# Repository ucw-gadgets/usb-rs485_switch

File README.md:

# usb-rs485_switch
8x RS-485 switch and USB convertor

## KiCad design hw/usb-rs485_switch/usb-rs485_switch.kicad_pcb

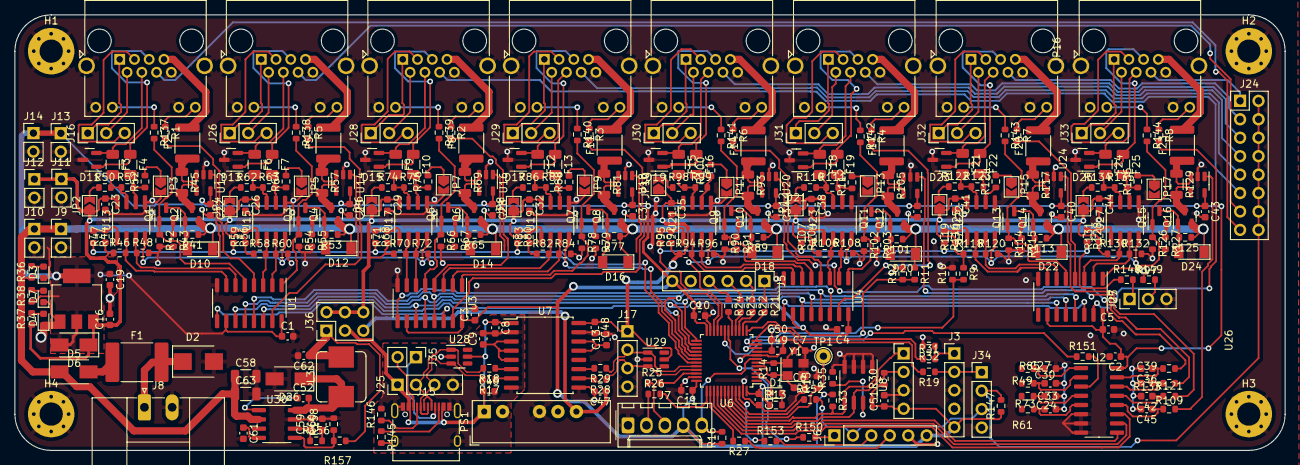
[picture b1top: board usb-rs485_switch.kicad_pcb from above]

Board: 2 copper layers, 175.0 x 60.0 mm, 357 parts (0 on the bottom side), 279 nets.

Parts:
C1, C2, C3, C4, C5, C8, C9, C10, C11, C12, C13, C22, C23, C24, C25, C26, C27, C28, C29, C30, C31, C32, C33, C34, C35, C36, C37, C38, C39, C40, C41, C42, C43, C44, C45, C48, C49, C51, C52: 100n; C_0603_1608Metric
C6, C7: C; C_0603_1608Metric
C16, C47: 10u; C_0603_1608Metric
C19: 22u; C_0603_1608Metric
C46: 4u7; C_0603_1608Metric
C50: 1u; C_0603_1608Metric
C58, C63: 4u7/50V; C_1206_3216Metric
C59, C61: 8.2n; C_0603_1608Metric
C60: 22n; C_0603_1608Metric
C62: 22u/6.3V X5R; C_0603_1608Metric
D1: USR_LED; LED_0603_1608Metric
D2: SM6T27A; D_SMB
D3: VCC_LED; LED_0603_1608Metric
D4: 5V_LED; LED_0603_1608Metric
D5, D6: SS54; D_SMA
D7: 3V3_LED; LED_0603_1608Metric
D10, D12, D14, D16, D18, D20, D22, D24: ZMM5V6; D_MiniMELF
D11, D13, D15, D17, D19, D21, D23, D25: PSM712-LF-T7; SOT-23
D26: SS14; D_SMA
F1: Polyfuse; Fuse_2920_7451Metric
F2, F5, F8, F11, F14, F17, F20, F23: BSMD1812-110-33V; Fuse_1812_4532Metric
F3, F4, F6, F7, F9, F10, F12, F13, F15, F16, F18, F19, F21, F22, F24, F25: BSMD1206-010-60V; Fuse_1206_3216Metric
H1, H2, H3, H4: MountingHole_Pad; MountingHole_3.2mm_M3_Pad_Via
J1, J2, J18, J19, J20, J21, J22, J23: RJ45_LED_Shielded; RJ45_Amphenol_RJHSE538X
J3: USART2; PinHeader_1x05_P2.54mm_Vertical
J4: I2C; PinHeader_1x04_P2.54mm_Vertical
J5: SPI; PinHeader_1x06_P2.54mm_Vertical
J6: GPIO; PinHeader_1x06_P2.54mm_Vertical
J7: PROG; Molex_KK-254_AE-6410-05A_1x05_P2.54mm_Vertical
J8: POWER; PhoenixContact_MC_1,5_2-GF-3.81_1x02_P3.81mm_Horizontal_Thr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
J9: VCC_OUT1; PinHeader_1x02_P2.54mm_Vertical
J10: VCC_OUT2; PinHeader_1x02_P2.54mm_Vertical
J11: 5V_OUT1; PinHeader_1x02_P2.54mm_Vertical
J12: 5V_OUT2; PinHeader_1x02_P2.54mm_Vertical
J13: 3V_OUT1; PinHeader_1x02_P2.54mm_Vertical
J14: 3V3_OUT2; PinHeader_1x02_P2.54mm_Vertical
J15: MC-107DM; USB_C_Receptacle_XKB_U262-16XN-4BVC11
J16: RES1; PinHeader_1x03_P2.54mm_Vertical
J17: USB_NONISO; PinHeader_1x04_P2.54mm_Vertical
J24: 1WIRE_CHANNELS; PinHeader_2x08_P2.54mm_Vertical
J25: USB_ISO; PinHeader_1x04_P2.54mm_Vertical
J26: RES2; PinHeader_1x03_P2.54mm_Vertical
J27: USART3; PinHeader_1x03_P2.54mm_Vertical
J28: RES3; PinHeader_1x03_P2.54mm_Vertical
J29: RES4; PinHeader_1x03_P2.54mm_Vertical
J30: RES5; PinHeader_1x03_P2.54mm_Vertical
J31: RES6; PinHeader_1x03_P2.54mm_Vertical
J32: RES7; PinHeader_1x03_P2.54mm_Vertical
J33: RES8; PinHeader_1x03_P2.54mm_Vertical
J34: 1WIRE_SELECT; PinHeader_1x04_P2.54mm_Vertical
J35: USB-C_SBU; PinHeader_1x02_P2.54mm_Vertical
J36: PWR_SELECT; PinHeader_2x03_P2.54mm_Vertical
JP2, JP3, JP4, JP5, JP6, JP7, JP8, JP9, JP10, JP11, JP12, JP13, JP14, JP15, JP16, JP17: SolderJumper_2_Open; SolderJumper-2_P1.3mm_Open_TrianglePad1.0x1.5mm
L3: 47u; L_Bourns_SRP7028A_7.3x6.6mm
PS1: IA0505S; Converter_DCDC_XP_POWER-IAxxxxS_THT
Q1, Q3, Q5, Q7, Q9, Q11, Q13, Q15: MMBT5551; SOT-23
Q2, Q4, Q6, Q8, Q10, Q12, Q14, Q16: Si2301CDS; SOT-23
R1, R2, R3, R4, R5, R6, R7, R8, R41, R53, R65, R77, R89, R101, R113, R125: 1k; R_0603_1608Metric
R9, R10, R11, R12, R13, R14, R15, R16, R31, R32, R35, R36, R37, R38, R148, R149, R156, R157, R158: R; R_0603_1608Metric
R17, R18, R28, R29: 24R; R_0603_1608Metric
R19, R21, R22, R23, R24, R25, R26, R27, R44, R56, R68, R80, R92, R104, R116, R128, R150, R151, R152, R153: 330R; R_0603_1608Metric
R30, R33, R147: 4k7; R_0603_1608Metric
R42, R46, R47, R48, R54, R58, R59, R60, R66, R70, R71, R72, R78, R82, R83, R84, R90, R94, R95, R96, R102, R106, R107, R108, R114, R118, R119, R120, R126, R130, R131, R132: 10k; R_0603_1608Metric
R43, R55, R67, R79, R91, R103, R115, R127, R137, R138, R139, R140, R141, R142, R143, R144: 2k7; R_0603_1608Metric
R45, R57, R69, R81, R93, R105, R117, R129: 0R1; R_1206_3216Metric
R49, R61, R73, R85, R97, R109, R121, R133: 100k; R_0603_1608Metric
R50, R52, R62, R64, R74, R76, R86, R88, R98, R100, R110, R112, R122, R124, R134, R136: 720R; R_0603_1608Metric
R51, R63, R75, R87, R99, R111, R123, R135: 120R; R_0603_1608Metric
R145, R146: 5k1; R_0603_1608Metric
TP1: BOOT0; TestPoint_THTPad_D2.0mm_Drill1.0mm
U1, U3, U4, U5: 74HC595; SOIC-16_3.9x9.9mm_P1.27mm
U2: CD4051B; SOIC-16_3.9x9.9mm_P1.27mm
U6: STM32F103C8Tx; LQFP-48_7x7mm_P0.5mm
U7: ADUM4160; SOIC-16W_7.5x10.3mm_P1.27mm
U8: M24C01-WMN; SOIC-8_3.9x4.9mm_P1.27mm
U11: AMS1117-3.3; SOT-223-3_TabPin2
U12, U14, U16, U18, U20, U22, U24, U26: INA180A1; SOT-23-5
U13, U15, U17, U19, U21, U23, U25, U27: MAX485E; SOIC-8_3.9x4.9mm_P1.27mm
U28, U29: SRV05-4; SOT-23-6
U30: TPS54331; SOIC-8_3.9x4.9mm_P1.27mm
Y1: Crystal_GND23; Crystal_SMD_3225-4Pin_3.2x2.5mm

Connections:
+3V3: C1.1, C2.1, C3.1, C4.1, C5.1, C10.1, C11.1, C12.1, C19.1, C22.1, C25.1, C28.1, C31.1, C34.1, C37.1, C40.1, C43.1, C49.1, C50.1, C51.1, D6.2 (A), J3.5, J4.4, J5.6, J6.6, J7.4, J13.1, J14.1, R13.1, R16.1, R30.1, R33.1, R38.1, R147.1, U1.10 (~SRCLR), U1.16 (VCC), U2.16 (VDD), U3.10 (~SRCLR), U3.16 (VCC), U4.10 (~SRCLR), U4.16 (VCC), U5.10 (~SRCLR), U5.16 (VCC), U6.9 (VDDA), U6.24 (VDD), U6.36 (VDD), U6.48 (VDD), U8.8 (VCC), U11.2 (VO), U12.5 (VS), U14.5 (VS), U16.5 (VS), U18.5 (VS), U20.5 (VS), U22.5 (VS), U24.5 (VS), U26.5 (VS)
+5V: C16.1, C23.1, C26.1, C29.1, C32.1, C35.1, C38.1, C41.1, C44.1, C48.1, D6.1 (K), J11.1, J12.1, J17.1, J36.2, J36.4, J36.6, JP2.1 (A), JP4.1 (A), JP6.1 (A), JP8.1 (A), JP10.1 (A), JP12.1 (A), JP14.1 (A), JP16.1 (A), R9.1, R37.1, R46.1, R47.1, R58.1, R59.1, R70.1, R71.1, R82.1, R83.1, R94.1, R95.1, R106.1, R107.1, R118.1, R119.1, R130.1, R131.1, U7.16 (VBUS2), U11.3 (VI), U13.8 (VCC), U15.8 (VCC), U17.8 (VCC), U19.8 (VCC), U21.8 (VCC), U23.8 (VCC), U25.8 (VCC), U27.8 (VCC), U29.5 (VP)
/1WIRE: J24.2, J24.4, J24.6, J24.8, J24.10, J24.12, J24.14, J24.16, J34.2, R147.2
/1WIRE1: J1.6, J24.15
/1WIRE2: J2.6, J24.13
/1WIRE3: J18.6, J24.11
/1WIRE4: J19.6, J24.9
/1WIRE5: J20.6, J24.7
/1WIRE6: J21.6, J24.5
/1WIRE7: J22.6, J24.3
/1WIRE8: J23.6, J24.1
/5V_DCDC: C62.1, J36.1, L3.2, R157.1
/5V_SENSE: R9.2, R10.1, U6.11 (PA1)
/5V_USB_ISO: C47.1, J36.5, PS1.6 (+Vout)
/GPIO0: J6.1, R150.2
/GPIO1: J6.2, J34.3, R152.2
/GPIO2: J6.3, R153.2
/GPIO3: J6.4, R27.1
/I2C1_SCL: J4.2, R30.2, U6.42 (PB6), U8.6 (SCL)
/I2C1_SDA: J4.1, R33.2, U6.43 (PB7), U8.5 (SDA)
/I_SENSE: R151.2, U2.3 (X)
/I_SENSE1: C24.1, R49.1, U2.1 (X4)
/I_SENSE2: C27.1, R61.1, U2.5 (X5)
/I_SENSE3: C30.1, R73.1, U2.2 (X6)
/I_SENSE4: C33.1, R85.1, U2.4 (X7)
/I_SENSE5: C36.1, R97.1, U2.15 (X2)
/I_SENSE6: C39.1, R109.1, U2.14 (X1)
/I_SENSE7: C42.1, R121.1, U2.13 (X0)
/I_SENSE8: C45.1, R133.1, U2.12 (X3)
/I_SEN_A: U2.11 (A), U6.39 (PB3)
/I_SEN_B: U2.10 (B), U6.40 (PB4)
/I_SEN_C: U2.9 (C), U6.41 (PB5)
/LED_G1: J1.12, R1.1
/LED_G2: J2.12, R5.1
/LED_G3: J18.12, R2.1
/LED_G4: J19.12, R3.1
/LED_G5: J20.12, R6.1
/LED_G6: J21.12, R4.1
/LED_G7: J22.12, R7.1
/LED_G8: J23.12, R8.1
/NRST: J7.5, R16.2, U6.7 (NRST)
/PWR_EN1: Q1.1 (B), R42.1, R137.2, U1.5 (QF)
/PWR_EN2: Q3.1 (B), R54.1, R138.2, U1.1 (QB)
/PWR_EN3: Q5.1 (B), R66.1, R139.2, U3.5 (QF)
/PWR_EN4: Q7.1 (B), R78.1, R140.2, U3.1 (QB)
/PWR_EN5: Q9.1 (B), R90.1, R141.2, U4.5 (QF)
/PWR_EN6: Q11.1 (B), R102.1, R142.2, U4.1 (QB)
/PWR_EN7: Q13.1 (B), R114.1, R143.2, U5.5 (QF)
/PWR_EN8: Q15.1 (B), R126.1, R144.2, U5.1 (QB)
/RS485 Line driver/A: D11.1 (A1), F4.1, J1.5
/RS485 Line driver/B: D11.2 (A2), F3.1, J1.4
/RS485 Line driver/PWR_OUT: F2.2, J1.7
/SPI1_MISO: J5.3, R23.1
/SPI1_MOSI: J5.4, R24.1
/SPI1_SCK: J5.2, R22.1
/SPI2_MOSI: U1.14 (SER), U6.28 (PB15)
/SPI2_SCK: U1.11 (SRCLK), U3.11 (SRCLK), U4.11 (SRCLK), U5.11 (SRCLK), U6.26 (PB13)
/SPI2_STROBE: U1.12 (RCLK), U3.12 (RCLK), U4.12 (RCLK), U5.12 (RCLK), U6.25 (PB12)
/SWCLK: J7.2, R26.1
/SWDIO: J7.3, R25.1
/TX_EN1: R48.1, U1.6 (QG), U13.3 (DE)
/TX_EN2: R60.1, U1.2 (QC), U15.3 (DE)
/TX_EN3: R72.1, U3.6 (QG), U17.3 (DE)
/TX_EN4: R84.1, U3.2 (QC), U19.3 (DE)
/TX_EN5: R96.1, U4.6 (QG), U21.3 (DE)
/TX_EN6: R108.1, U4.2 (QC), U23.3 (DE)
/TX_EN7: R120.1, U5.6 (QG), U25.3 (DE)
/TX_EN8: R132.1, U5.2 (QC), U27.3 (DE)
/USART1_RX: R44.2, R56.2, R68.2, R80.2, U6.31 (PA10)
/USART1_TX: U6.30 (PA9), U13.4 (DI), U15.4 (DI), U17.4 (DI), U19.4 (DI)
/USART2_RX: R31.1, U6.13 (PA3)
/USART2_TX: J3.2, J34.1, R19.1
/USART3_RX: R92.2, R104.2, R116.2, R128.2, R148.1, U6.22 (PB11)
/USART3_TX: R149.1, U6.21 (PB10), U21.4 (DI), U23.4 (DI), U25.4 (DI), U27.4 (DI)
/USB_DN: J17.2, R29.1, U6.32 (PA11), U29.1 (IO1)
/USB_DP: J17.3, R28.1, U6.33 (PA12), U29.3 (IO2)
/USB_IN_N: J15.A7 (D-), J15.B7 (D-), J25.2, R18.2, U28.1 (IO1)
/USB_IN_P: J15.A6 (D+), J15.B6 (D+), J25.3, R17.2, U28.3 (IO2)
/VCC_SENSE: R11.2, R12.1, U6.10 (PA0)
/sheet620AF7C7/A: D17.1 (A1), F13.1, J19.5
/sheet620AF7C7/B: D17.2 (A2), F12.1, J19.4
/sheet620AF7C7/PWR_OUT: F11.2, J19.7
/sheet620CBEF1/A: D19.1 (A1), F16.1, J20.5
/sheet620CBEF1/B: D19.2 (A2), F15.1, J20.4
/sheet620CBEF1/PWR_OUT: F14.2, J20.7
/sheet620CBEF2/A: D21.1 (A1), F19.1, J21.5
/sheet620CBEF2/B: D21.2 (A2), F18.1, J21.4
/sheet620CBEF2/PWR_OUT: F17.2, J21.7
/sheet620CBEF3/A: D23.1 (A1), F22.1, J22.5
/sheet620CBEF3/B: D23.2 (A2), F21.1, J22.4
/sheet620CBEF3/PWR_OUT: F20.2, J22.7
/sheet620CBEF4/A: D25.1 (A1), F25.1, J23.5
/sheet620CBEF4/B: D25.2 (A2), F24.1, J23.4
/sheet620CBEF4/PWR_OUT: F23.2, J23.7
/sheet6205AD21/A: D13.1 (A1), F7.1, J2.5
/sheet6205AD21/B: D13.2 (A2), F6.1, J2.4
/sheet6205AD21/PWR_OUT: F5.2, J2.7
/sheet62070CF7/A: D15.1 (A1), F10.1, J18.5
/sheet62070CF7/B: D15.2 (A2), F9.1, J18.4
/sheet62070CF7/PWR_OUT: F8.2, J18.7
/~RX_EN1: R46.2, U1.7 (QH), U13.2 (~RE)
/~RX_EN2: R58.2, U1.3 (QD), U15.2 (~RE)
/~RX_EN3: R70.2, U3.7 (QH), U17.2 (~RE)
/~RX_EN4: R82.2, U3.3 (QD), U19.2 (~RE)
/~RX_EN5: R94.2, U4.7 (QH), U21.2 (~RE)
/~RX_EN6: R106.2, U4.3 (QD), U23.2 (~RE)
/~RX_EN7: R118.2, U5.7 (QH), U25.2 (~RE)
/~RX_EN8: R130.2, U5.3 (QD), U27.2 (~RE)
/~SPI1_SS: J5.1, R21.1
/~SPI2_OE: U1.13 (~OE), U3.13 (~OE), U4.13 (~OE), U5.13 (~OE), U6.29 (PA8)
GND: C1.2, C2.2, C3.2, C4.2, C5.2, C6.2, C7.2, C10.2, C11.2, C12.2, C13.2, C16.2, C19.2, C22.2, C23.2, C24.2, C25.2, C26.2, C27.2, C28.2, C29.2, C30.2, C31.2, C32.2, C33.2, C34.2, C35.2, C36.2, C37.2, C38.2, C39.2, C40.2, C41.2, C42.2, C43.2, C44.2, C45.2, C47.2, C48.2, C49.2, C50.2, C51.2, C58.2, C59.2, C60.2, C61.2, C62.2, C63.2, D2.2 (A2), D3.1 (K), D4.1 (K), D7.1 (K), D11.3 (common), D13.3 (common), D15.3 (common), D17.3 (common), D19.3 (common), D21.3 (common), D23.3 (common), D25.3 (common), D26.2 (A), H1.1, H2.1, H3.1, H4.1, J1.8, J1.9, J1.11, J1.SH, J2.8, J2.9, J2.11, J2.SH, J3.3, J4.3, J5.5, J6.5, J7.1, J8.2, J9.2, J10.2, J11.2, J12.2, J13.2, J14.2, J17.4, J18.8, J18.9, J18.11, J18.SH, J19.8, J19.9, J19.11, J19.SH, J20.8, J20.9, J20.11, J20.SH, J21.8, J21.9, J21.11, J21.SH, J22.8, J22.9, J22.11, J22.SH, J23.8, J23.9, J23.11, J23.SH, J27.3, J34.4, JP3.2 (B), JP5.2 (B), JP7.2 (B), JP9.2 (B), JP11.2 (B), JP13.2 (B), JP15.2 (B), JP17.2 (B), PS1.4 (-Vout), R10.2, R12.2, R15.2, R32.2, R35.2, R42.2, R43.2, R48.2, R54.2, R55.2, R60.2, R66.2, R67.2, R72.2, R78.2, R79.2, R84.2, R90.2, R91.2, R96.2, R102.2, R103.2, R108.2, R114.2, R115.2, R120.2, R126.2, R127.2, R132.2, R158.2, U1.8 (GND), U2.6 (INH), U2.7 (VEE), U2.8 (VSS), U3.8 (GND), U4.8 (GND), U5.8 (GND), U6.8 (VSSA), U6.23 (VSS), U6.35 (VSS), U6.47 (VSS), U7.9 (GND2), U7.15 (GND2), U8.1 (E0), U8.2 (E1), U8.3 (E2), U8.4 (VSS), U11.1 (GND), U12.2 (GND), U13.5 (GND), U14.2 (GND), U15.5 (GND), U16.2 (GND), U17.5 (GND), U18.2 (GND), U19.5 (GND), U20.2 (GND), U21.5 (GND), U22.2 (GND), U23.5 (GND), U24.2 (GND), U25.5 (GND), U26.2 (GND), U27.5 (GND), U29.2 (VN), U30.7 (GND), Y1.2, Y1.3
GND2: C8.2, C9.2, C46.2, J15.A1 (GND), J15.A12 (GND), J15.B1 (GND), J15.B12 (GND), J15.S1 (SHIELD), J25.4, PS1.2 (-Vin), R145.2, R146.2, U7.2 (GND1), U7.8 (GND1), U28.2 (VN)
unnamed: C6.1, R14.1, U6.5 (PD0), Y1.1
unnamed: C7.1, R14.2, U6.6 (PD1), Y1.4
unnamed: C9.1, U7.3 (VDD1), U7.4 (PDEN), U7.5 (SPU)
unnamed: C13.1, U7.13 (SPD), U7.14 (VDD2)
unnamed: C52.2, D26.1 (K), L3.1, U30.8 (PH)
unnamed: C60.1, R156.2
unnamed: D1.1 (K), U6.2 (PC13)
unnamed: D1.2 (A), R13.2
unnamed: D2.1 (A1), F1.2, J8.1
unnamed: D3.2 (A), R36.2
unnamed: D4.2 (A), R37.2
unnamed: D5.2 (A), F1.1
unnamed: D7.2 (A), R38.2
unnamed: D10.2 (A), Q1.3 (C), Q2.1 (G), R41.2
unnamed: D12.2 (A), Q3.3 (C), Q4.1 (G), R53.2
unnamed: D14.2 (A), Q5.3 (C), Q6.1 (G), R65.2
unnamed: D16.2 (A), Q7.3 (C), Q8.1 (G), R77.2
unnamed: D18.2 (A), Q9.3 (C), Q10.1 (G), R89.2
unnamed: D20.2 (A), Q11.3 (C), Q12.1 (G), R101.2
unnamed: D22.2 (A), Q13.3 (C), Q14.1 (G), R113.2
unnamed: D24.2 (A), Q15.3 (C), Q16.1 (G), R125.2
unnamed: F2.1, R45.1, U12.3 (+)
unnamed: F3.2, R50.2, R51.1, U13.7 (B)
unnamed: F4.2, R51.2, R52.1, U13.6 (A)
unnamed: F5.1, R57.1, U14.3 (+)
unnamed: F6.2, R62.2, R63.1, U15.7 (B)
unnamed: F7.2, R63.2, R64.1, U15.6 (A)
unnamed: F8.1, R69.1, U16.3 (+)
unnamed: F9.2, R74.2, R75.1, U17.7 (B)
unnamed: F10.2, R75.2, R76.1, U17.6 (A)
unnamed: F11.1, R81.1, U18.3 (+)
unnamed: F12.2, R86.2, R87.1, U19.7 (B)
unnamed: F13.2, R87.2, R88.1, U19.6 (A)
unnamed: F14.1, R93.1, U20.3 (+)
unnamed: F15.2, R98.2, R99.1, U21.7 (B)
unnamed: F16.2, R99.2, R100.1, U21.6 (A)
unnamed: F17.1, R105.1, U22.3 (+)
unnamed: F18.2, R110.2, R111.1, U23.7 (B)
unnamed: F19.2, R111.2, R112.1, U23.6 (A)
unnamed: F20.1, R117.1, U24.3 (+)
unnamed: F21.2, R122.2, R123.1, U25.7 (B)
unnamed: F22.2, R123.2, R124.1, U25.6 (A)
unnamed: F23.1, R129.1, U26.3 (+)
unnamed: F24.2, R134.2, R135.1, U27.7 (B)
unnamed: F25.2, R135.2, R136.1, U27.6 (A)
unnamed: J1.1, J16.1
unnamed: J1.2, J16.2
unnamed: J1.3, J16.3
unnamed: J1.10, R137.1
unnamed: J2.1, J26.1
unnamed: J2.2, J26.2
unnamed: J2.3, J26.3
unnamed: J2.10, R138.1
unnamed: J3.1, R31.2, R32.1
unnamed: J15.A5 (CC1), R146.1
unnamed: J15.A8 (SBU1), J35.1
unnamed: J15.B5 (CC2), R145.1
unnamed: J15.B8 (SBU2), J35.2
unnamed: J18.1, J28.1
unnamed: J18.2, J28.2
unnamed: J18.3, J28.3
unnamed: J18.10, R139.1
unnamed: J19.1, J29.1
unnamed: J19.2, J29.2
unnamed: J19.3, J29.3
unnamed: J19.10, R140.1
unnamed: J20.1, J30.1
unnamed: J20.2, J30.2
unnamed: J20.3, J30.3
unnamed: J20.10, R141.1
unnamed: J21.1, J31.1
unnamed: J21.2, J31.2
unnamed: J21.3, J31.3
unnamed: J21.10, R142.1
unnamed: J22.1, J32.1
unnamed: J22.2, J32.2
unnamed: J22.3, J32.3
unnamed: J22.10, R143.1
unnamed: J23.1, J33.1
unnamed: J23.2, J33.2
unnamed: J23.3, J33.3
unnamed: J23.10, R144.1
unnamed: J27.1, R148.2
unnamed: J27.2, R149.2
unnamed: JP2.2 (B), R50.1
unnamed: JP3.1 (A), R52.2
unnamed: JP4.2 (B), R62.1
unnamed: JP5.1 (A), R64.2
unnamed: JP6.2 (B), R74.1
unnamed: JP7.1 (A), R76.2
unnamed: JP8.2 (B), R86.1
unnamed: JP9.1 (A), R88.2
unnamed: JP10.2 (B), R98.1
unnamed: JP11.1 (A), R100.2
unnamed: JP12.2 (B), R110.1
unnamed: JP13.1 (A), R112.2
unnamed: JP14.2 (B), R122.1
unnamed: JP15.1 (A), R124.2
unnamed: JP16.2 (B), R134.1
unnamed: JP17.1 (A), R136.2
unnamed: Q1.2 (E), R43.1
unnamed: Q2.3 (D), R45.2, U12.4 (-)
unnamed: Q3.2 (E), R55.1
unnamed: Q4.3 (D), R57.2, U14.4 (-)
unnamed: Q5.2 (E), R67.1
unnamed: Q6.3 (D), R69.2, U16.4 (-)
unnamed: Q7.2 (E), R79.1
unnamed: Q8.3 (D), R81.2, U18.4 (-)
unnamed: Q9.2 (E), R91.1
unnamed: Q10.3 (D), R93.2, U20.4 (-)
unnamed: Q11.2 (E), R103.1
unnamed: Q12.3 (D), R105.2, U22.4 (-)
unnamed: Q13.2 (E), R115.1
unnamed: Q14.3 (D), R117.2, U24.4 (-)
unnamed: Q15.2 (E), R127.1
unnamed: Q16.3 (D), R129.2, U26.4 (-)
unnamed: R7.2, U5.4 (QE)
unnamed: R8.2, U5.15 (QA)
unnamed: R15.1, TP1.1, U6.44 (BOOT0)
unnamed: R17.1, U7.7 (UD+)
unnamed: R18.1, U7.6 (UD-)
unnamed: R19.2, U6.12 (PA2)
unnamed: R21.2, U6.14 (PA4)
unnamed: R22.2, U6.15 (PA5)
unnamed: R23.2, U6.16 (PA6)
unnamed: R24.2, U6.17 (PA7)
unnamed: R25.2, U6.34 (PA13)
unnamed: R26.2, U6.37 (PA14)
unnamed: R27.2, U6.38 (PA15)
unnamed: R28.2, U7.10 (DD+)
unnamed: R29.2, U7.11 (DD-)
unnamed: R35.1, U8.7 (~WC)
unnamed: R44.1, R47.2, U13.1 (RO)
unnamed: R49.2, U12.1
unnamed: R56.1, R59.2, U15.1 (RO)
unnamed: R61.2, U14.1
unnamed: R68.1, R71.2, U17.1 (RO)
unnamed: R73.2, U16.1
unnamed: R80.1, R83.2, U19.1 (RO)
unnamed: R85.2, U18.1
unnamed: R92.1, R95.2, U21.1 (RO)
unnamed: R97.2, U20.1
unnamed: R104.1, R107.2, U23.1 (RO)
unnamed: R109.2, U22.1
unnamed: R116.1, R119.2, U25.1 (RO)
unnamed: R121.2, U24.1
unnamed: R128.1, R131.2, U27.1 (RO)
unnamed: R133.2, U26.1
unnamed: R150.1, U6.18 (PB0)
unnamed: R151.1, U6.19 (PB1)
unnamed: R152.1, U6.45 (PB8)
unnamed: R153.1, U6.46 (PB9)
unnamed: R1.2, U1.4 (QE)
unnamed: U1.9 (QH'), U3.14 (SER)
unnamed: R5.2, U1.15 (QA)
unnamed: R2.2, U3.4 (QE)
unnamed: R3.2, U3.15 (QA)
unnamed: R6.2, U4.4 (QE)
unnamed: U3.9 (QH'), U4.14 (SER)
unnamed: R4.2, U4.15 (QA)
unnamed: U4.9 (QH'), U5.14 (SER)
unnamed: C52.1, U30.1 (BOOT)
unnamed: C61.1, U30.4 (SS)
unnamed: R157.2, R158.1, U30.5 (VSENSE)
unnamed: C59.1, R156.1, U30.6 (COMP)
VBUS: C8.1, C46.1, J15.A4 (VBUS), J15.A9 (VBUS), J15.B4 (VBUS), J15.B9 (VBUS), J25.1, J36.3, PS1.1 (+Vin), U7.1 (VBUS1), U28.5 (VP)
VCC: C58.1, C63.1, D5.1 (K), D10.1 (K), D12.1 (K), D14.1 (K), D16.1 (K), D18.1 (K), D20.1 (K), D22.1 (K), D24.1 (K), J9.1, J10.1, Q2.2 (S), Q4.2 (S), Q6.2 (S), Q8.2 (S), Q10.2 (S), Q12.2 (S), Q14.2 (S), Q16.2 (S), R11.1, R36.1, R41.1, R53.1, R65.1, R77.1, R89.1, R101.1, R113.1, R125.1, U30.2 (VIN)

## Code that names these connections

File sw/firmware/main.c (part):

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
static void gpio_init(void)
{
	// PA0 = VCC sense -> ADC12_IN0
	// PA1 = 5V sense -> ADC12_IN1
	// PA2 = TXD2 (debug)
	// PA3 = RXD2
	// PA4 = SPI1_SS*  (jumpers)
	// PA5 = SPI1_SCK
	// PA6 = SPI1_MISO
	// PA7 = SPI1_MOSI
	// PA8 = SPI2_OE*
	// PA9 = TXD1
	// PA10 = RXD1
	// PA11 = USB_DN
	// PA12 = USB_DP
	// PA13 + PA14 = programming interface
	// PA15 = GPIO3

	// PB0 = GPIO0 = ADuM4160 PIN (USB upstream enable)
	// PB1 = I_SENSE -> ADC12_IN9
	// PB2 = unused
	// PB3 = I_SEN_A
	// PB4 = I_SEN_B
	// PB5 = I_SEN_C
	// PB6 = I2C1_SCL
	// PB7 = I2C1_SDA
	// PB8 = GPIO1
	// PB9 = GPIO2
	// PB10 = TXD3
	// PB11 = RXD3
	// PB12 = SPI2_STROBE
	// PB13 = SPI2_SCK
	// PB14 = SPI2_MISO
	// PB15 = SPI2_MOSI

	// PC13 = debugging LED *
	// PC14 = unused
	// PC15 = unused

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
static void debug_init(void)
{
	// PC13 = debugging LED à la BluePill
	gpio_set_mode(GPIOC, GPIO_MODE_OUTPUT_50_MHZ, GPIO_CNF_OUTPUT_PUSHPULL, GPIO13);
	gpio_clear(GPIOC, GPIO13);

	// USART2: Debugging console
	// PA2 = TXD2
	// PA3 = RXD2
	gpio_set_mode(GPIOA, GPIO_MODE_OUTPUT_50_MHZ, GPIO_CNF_OUTPUT_ALTFN_PUSHPULL, GPIO2);
	gpio_set_mode(GPIOA, GPIO_MODE_INPUT, GPIO_CNF_INPUT_FLOAT, GPIO3);

	usart_set_baudrate(USART2, 115200);
	usart_set_databits(USART2, 8);
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
static void reg_init(void)
{
	// Pins: PA8=OE*, PB12=STROBE, PB13=SCK, PB14=MISO, PB15=MOSI
	gpio_set_mode(GPIOA, GPIO_MODE_OUTPUT_50_MHZ, GPIO_CNF_OUTPUT_PUSHPULL, GPIO8);
	gpio_set_mode(GPIOB, GPIO_MODE_OUTPUT_50_MHZ, GPIO_CNF_OUTPUT_PUSHPULL, GPIO12);
	gpio_set_mode(GPIOB, GPIO_MODE_OUTPUT_50_MHZ, GPIO_CNF_OUTPUT_ALTFN_PUSHPULL, GPIO13 | GPIO15);
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
static void adc_init(void)
{
	// PA0, PA1 and PB1 are analog inputs
	gpio_set_mode(GPIOA, GPIO_MODE_INPUT, GPIO_CNF_INPUT_ANALOG, GPIO0 | GPIO1);
	gpio_set_mode(GPIOB, GPIO_MODE_INPUT, GPIO_CNF_INPUT_ANALOG, GPIO1);

	// PB3 to PB5 control the analog multiplexer on PB1
	gpio_set_mode(GPIOB, GPIO_MODE_OUTPUT_50_MHZ, GPIO_CNF_OUTPUT_PUSHPULL, GPIO3 | GPIO4 | GPIO5);

	adc_power_off(ADC1);
	// ADC prescaler set by rcc_clock_setup_pll(): ADC clock = PCLK2/8 = 9 MHz
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
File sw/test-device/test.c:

/*
 *	An Example MODBUS Client on the BluePill
 *
 *	Pin assignment:
 *
 *		PA2	TXD2 (debugging console)
 *		PA3	RXD2 (debugging console)
 *		PB1	transceiver DE
 *		PB10	TXD3 -> transceiver D
 *		PB11	RXD3 -> transceiver R
 */

#include "util.h"
#include "modbus.h"

#include <libopencm3/cm3/cortex.h>
#include <libopencm3/cm3/nvic.h>
#include <libopencm3/cm3/systick.h>
#include <libopencm3/stm32/rcc.h>
#include <libopencm3/stm32/gpio.h>
#include <libopencm3/stm32/usart.h>
#include <libopencm3/stm32/timer.h>

static void clock_setup(void)
{
	rcc_clock_setup_pll(&rcc_hse_configs[RCC_CLOCK_HSE8_72MHZ]);

	rcc_periph_clock_enable(RCC_GPIOA);
	rcc_periph_clock_enable(RCC_GPIOB);
	rcc_periph_clock_enable(RCC_GPIOC);
	rcc_periph_clock_enable(RCC_USART2);
	rcc_periph_clock_enable(RCC_USART3);
	rcc_periph_clock_enable(RCC_TIM2);
	rcc_periph_clock_enable(RCC_TIM4);

	rcc_periph_reset_pulse(RST_GPIOA);
	rcc_periph_reset_pulse(RST_GPIOB);
	rcc_periph_reset_pulse(RST_GPIOC);
	rcc_periph_reset_pulse(RST_USART2);
	rcc_periph_reset_pulse(RST_USART3);
	rcc_periph_reset_pulse(RST_TIM2);
	rcc_periph_reset_pulse(RST_TIM4);
}

static void gpio_setup(void)
{
	// PC13 = BluePill LED
	gpio_set_mode(GPIOC, GPIO_MODE_OUTPUT_50_MHZ, GPIO_CNF_OUTPUT_PUSHPULL, GPIO13);
	gpio_clear(GPIOC, GPIO13);

	// Pins for MODBUS USART
	gpio_set_mode(GPIOB, GPIO_MODE_INPUT, GPIO_CNF_INPUT_FLOAT, GPIO_USART3_RX);
	gpio_set_mode(GPIOB, GPIO_MODE_OUTPUT_50_MHZ, GPIO_CNF_OUTPUT_ALTFN_PUSHPULL, GPIO_USART3_TX);
	gpio_set_mode(GPIOB, GPIO_MODE_OUTPUT_50_MHZ, GPIO_CNF_OUTPUT_PUSHPULL, GPIO1);
}

static volatile u32 ms_ticks;

void sys_tick_handler(void)
{
	ms_ticks++;
}

static void tick_setup(void)
{
	systick_set_frequency(1000, 72000000);
	systick_counter_enable();
	systick_interrupt_enable();
}

static void delay_ms(uint ms)
{
	u32 start_ticks = ms_ticks;
	while (ms_ticks - start_ticks < ms)
		;
}

static void debug_setup(void)
{
	gpio_set_mode(GPIOA, GPIO_MODE_OUTPUT_50_MHZ, GPIO_CNF_OUTPUT_ALTFN_PUSHPULL, GPIO_USART2_TX);
	gpio_set_mode(GPIOA, GPIO_MODE_INPUT, GPIO_CNF_INPUT_FLOAT, GPIO_USART2_RX);

	usart_set_baudrate(USART2, 115200);
	usart_set_databits(USART2, 8);
	usart_set_stopbits(USART2, USART_STOPBITS_1);
	usart_set_mode(USART2, USART_MODE_TX_RX);
	usart_set_parity(USART2, USART_PARITY_NONE);
	usart_set_flow_control(USART2, USART_FLOWCONTROL_NONE);

	usart_enable(USART2);
}

int main(void)
{
	clock_setup();
	gpio_setup();
	tick_setup();
	debug_setup();
	debug_printf("Chramst!\n");

	modbus_init();
	cm_enable_interrupts();

	for (;;) {
		debug_led_toggle();
		delay_ms(50);
		modbus_loop();
	}

	return 0;
}

/*** Modbus callbacks ***/

bool modbus_check_discrete_input(u16 addr UNUSED)
{
	return false;
}

bool modbus_get_discrete_input(u16 addr UNUSED)
{
	return false;
}

bool modbus_check_coil(u16 addr UNUSED)
{
	return false;
}

bool modbus_get_coil(u16 addr UNUSED)
{
	return false;
}

void modbus_set_coil(u16 addr UNUSED, bool value UNUSED)
{
}

bool modbus_check_input_register(u16 addr UNUSED)
{
	return false;
}

u16 modbus_get_input_register(u16 addr UNUSED)
{
	return 0;
}

bool modbus_check_holding_register(u16 addr UNUSED)
{
	return (addr < 16);
}

u16 modbus_get_holding_register(u16 addr UNUSED)
{
	return 0xbeef;
}

void modbus_set_holding_register(u16 addr UNUSED, u16 value UNUSED)
{
}

void modbus_ready_hook(void)
{
}

void modbus_frame_start_hook(void)
{
}

const char * const modbus_id_strings[MODBUS_ID_MAX] = {
	[MODBUS_ID_VENDOR_NAME] = "United Computer Wizards",
	[MODBUS_ID_PRODUCT_CODE] = "42",
	[MODBUS_ID_MAJOR_MINOR_REVISION] = "1.0",
	[MODBUS_ID_VENDOR_URL] = "http://www.ucw.cz/",
	[MODBUS_ID_PRODUCT_NAME] = "Magic Gadget",
	[MODBUS_ID_USER_APP_NAME] = NULL,
};

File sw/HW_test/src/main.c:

/*
 * This file is part of the libopencm3 project.
 *
 * Copyright (C) 2009 Uwe Hermann <uwe@hermann-uwe.de>
 * Copyright (C) 2013 Stephen Dwyer <scdwyer@ualberta.ca>
 *
 * This library is free software: you can redistribute it and/or modify
 * it under the terms of the GNU Lesser General Public License as published by
 * the Free Software Foundation, either version 3 of the License, or
 * (at your option) any later version.
 *
 * This library is distributed in the hope that it will be useful,
 * but WITHOUT ANY WARRANTY; without even the implied warranty of
 * MERCHANTABILITY or FITNESS FOR A PARTICULAR PURPOSE.  See the
 * GNU Lesser General Public License for more details.
 *
 * You should have received a copy of the GNU Lesser General Public License
 * along with this library.  If not, see <http://www.gnu.org/licenses/>.
 */
#if 0
#include <libopencm3/stm32/rcc.h>
#include <libopencm3/stm32/gpio.h>
#include <libopencm3/stm32/usart.h>
#include <libopencm3/stm32/dma.h>
#include <libopencm3/cm3/nvic.h>
#include <libopencm3/stm32/spi.h>
#include <stdio.h>
#include <errno.h>

int _write(int file, char *ptr, int len);

static void clock_setup(void)
{
	rcc_clock_setup_in_hse_8mhz_out_72mhz();

	/* Enable GPIOA, GPIOB, GPIOC clock. */
	rcc_periph_clock_enable(RCC_GPIOA);
	rcc_periph_clock_enable(RCC_GPIOB);
	rcc_periph_clock_enable(RCC_GPIOC);

	/* Enable clocks for GPIO port A (for GPIO_USART2_TX) and USART2. */
	rcc_periph_clock_enable(RCC_GPIOA);
	rcc_periph_clock_enable(RCC_AFIO);
	rcc_periph_clock_enable(RCC_USART1);
	rcc_periph_clock_enable(RCC_USART2);
	rcc_periph_clock_enable(RCC_USART3);

	/* Enable SPI2 Periph and gpio clocks */
	rcc_periph_clock_enable(RCC_SPI2);
}

static void spi_setup(void) {

  /* Configure GPIOs: SS=PA4, SCK=PA5, MISO=PA6 and MOSI=PA7 */
  gpio_set_mode(GPIOB, GPIO_MODE_OUTPUT_50_MHZ,
            GPIO_CNF_OUTPUT_ALTFN_PUSHPULL, GPIO13 | GPIO15);
  gpio_set_mode(GPIOA,GPIO_MODE_OUTPUT_50_MHZ, GPIO_CNF_OUTPUT_PUSHPULL,GPIO8);
  gpio_set_mode(GPIOB,GPIO_MODE_OUTPUT_50_MHZ, GPIO_CNF_OUTPUT_PUSHPULL,GPIO12);

  /* Reset SPI, SPI_CR1 register cleared, SPI is disabled */
  spi_reset(SPI2);

  /* Set up SPI in Master mode with:
   * Clock baud rate: 1/64 of peripheral clock frequency
   * Clock polarity: Idle High
   * Clock phase: Data valid on 2nd clock pulse
   * Data frame format: 8-bit
   * Frame format: MSB First
   */
  spi_init_master(SPI2, SPI_CR1_BAUDRATE_FPCLK_DIV_64, SPI_CR1_CPOL_CLK_TO_1_WHEN_IDLE,
                  SPI_CR1_CPHA_CLK_TRANSITION_2, SPI_CR1_DFF_8BIT, SPI_CR1_MSBFIRST);

  /*
   * Set NSS management to software.
   *
   * Note:
   * Setting nss high is very important, even if we are controlling the GPIO
   * ourselves this bit needs to be at least set to 1, otherwise the spi
   * peripheral will not send any data out.
   */
  spi_enable_software_slave_management(SPI2);
  spi_set_nss_high(SPI2);

  /* Enable SPI2 periph. */
  spi_enable(SPI2);
}

static void usart_setup(void)
{
	/* Setup GPIO pin GPIO_USART2_TX and GPIO_USART2_RX. */
	gpio_set_mode(GPIOA, GPIO_MODE_OUTPUT_50_MHZ,
		      GPIO_CNF_OUTPUT_ALTFN_PUSHPULL, GPIO_USART2_TX);
	gpio_set_mode(GPIOA, GPIO_MODE_INPUT,
		      GPIO_CNF_INPUT_FLOAT, GPIO_USART2_RX);

	/* Setup UART parameters. */
	usart_set_baudrate(USART2, 9600);
	usart_set_databits(USART2, 8);
	usart_set_stopbits(USART2, USART_STOPBITS_1);
	usart_set_mode(USART2, USART_MODE_TX_RX);
	usart_set_parity(USART2, USART_PARITY_NONE);
	usart_set_flow_control(USART2, USART_FLOWCONTROL_NONE);

	/* Finally enable the USART. */
	usart_enable(USART2);
	
	/* Setup GPIO pin GPIO_USART3_TX and GPIO_USART3_RX. */
	gpio_set_mode(GPIO_BANK_USART3_TX, GPIO_MODE_OUTPUT_50_MHZ,
		      GPIO_CNF_OUTPUT_ALTFN_PUSHPULL, GPIO_USART3_TX);
	gpio_set_mode(GPIO_BANK_USART3_RX, GPIO_MODE_INPUT,
		      GPIO_CNF_INPUT_FLOAT, GPIO_USART3_RX);

	/* Setup UART parameters. */
	usart_set_baudrate(USART3, 9600);
	usart_set_databits(USART3, 8);
	usart_set_stopbits(USART3, USART_STOPBITS_1);
	usart_set_mode(USART3, USART_MODE_TX_RX);
	usart_set_parity(USART3, USART_PARITY_NONE);
	usart_set_flow_control(USART3, USART_FLOWCONTROL_NONE);

	/* Finally enable the USART. */
	usart_enable(USART3);
	
	/* Setup GPIO pin GPIO_USART1_TX and GPIO_USART1_RX. */
	gpio_set_mode(GPIO_BANK_USART1_TX, GPIO_MODE_OUTPUT_50_MHZ,
		      GPIO_CNF_OUTPUT_ALTFN_PUSHPULL, GPIO_USART1_TX);
	gpio_set_mode(GPIO_BANK_USART1_RX, GPIO_MODE_INPUT,
		      GPIO_CNF_INPUT_FLOAT, GPIO_USART1_RX);

	/* Setup UART parameters. */
	usart_set_baudrate(USART1, 9600);
	usart_set_databits(USART1, 8);
	usart_set_stopbits(USART1, USART_STOPBITS_1);
	usart_set_mode(USART1, USART_MODE_TX_RX);
	usart_set_parity(USART1, USART_PARITY_NONE);
	usart_set_flow_control(USART1, USART_FLOWCONTROL_NONE);

	/* Finally enable the USART. */
	usart_enable(USART1);
}

int _write(int file, char *ptr, int len)
{
	int i;

	if (file == 1) {
		for (i = 0; i < len; i++)
			usart_send_blocking(USART2, ptr[i]);
		return i;
	}

	errno = EIO;
	return -1;
}

static void gpio_setup(void)
{
	/* Set GPIO8 (in GPIO port A) to 'output push-pull'. */
	gpio_set_mode(GPIOC, GPIO_MODE_OUTPUT_2_MHZ,
		      GPIO_CNF_OUTPUT_PUSHPULL, GPIO13);
}

int main(void)
{
	int counter = 0;
	uint16_t rx_value = 0x42;

	clock_setup();
	gpio_setup();
	usart_setup();
	spi_setup();


	/* Blink the LED (PA8) on the board with every transmitted byte. */
	while (1) {
		/* LED on/off */
		gpio_toggle(GPIOC, GPIO13);
		 
		//gpio_toggle(GPIOA, GPIO8);

		spi_send(SPI2, (uint8_t) 0x7);
		for (int i=0;i<4;i++){

			gpio_set(GPIOB,GPIO12);
			int j=0;
			while(j<1000L){
				asm("nop");
				j++;
			}
			gpio_clear(GPIOB,GPIO12);

			/* printf the value that SPI should send */
			//printf("Counter: %i  SPI Sent Byte: %i", counter, (uint8_t) counter);
			/* blocking send of the byte out SPI2 */
			spi_send(SPI2, (uint8_t) 0x00);
			gpio_set(GPIOB,GPIO12);
			j=0;
			while(j<1000L){
				asm("nop");
				j++;
			}
			gpio_clear(GPIOB,GPIO12);
			/* Read the byte that just came in (use a loopback between MISO and MOSI
			* to get the same byte back)
			*/
			//rx_value = spi_read(SPI2);
			/* printf the byte just received */
			//printf("    SPI Received Byte: %i\r\n", rx_value);

			//counter++;
			j=0;
			while(j<10000000L){
				asm("nop");
				j++;
			}

			usart_send_blocking(USART1,'1');
			usart_send_blocking(USART2,'2');
			usart_send_blocking(USART3,'3');
		}
		
	}

	return 0;
}
#endif

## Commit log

2021-06-12 WIP schematic
2021-11-23 Schematic WIP.
2021-12-22 Progress in schematic.
2021-12-28 Migration to KiCAD 6, finished schematic.
2022-01-03 Added 1wire and power selection jumpers.
2022-01-20 Assigned footprints, started routing.
2022-01-25 Routing in progress.
2022-01-27 Routing in progress...
2022-01-30 Routed.
2022-02-03 Removed unused DCDC, board labels.
2022-02-05 Final changes.
2022-03-12 Added some code for HW testing.
2022-03-12 MJ's test software
2022-03-12 mjtest: Manual control of port power
2022-06-18 mjtest: Povoleno USB
2022-06-20 TODO: Hardware fixes
2022-06-20 mjtest: USB works
2022-06-22 mjtest: Testing ADC
2022-06-24 mjtest: Fix ADC tests
2022-06-24 mjtest: Fix ADC clock
2022-06-25 mjtest: Do not forget to remap pins used by JTAG by default
2022-06-25 TODO: Brighten green LEDs
2022-06-25 TODO: Bugs in current measurement circuitry
2022-06-25 mjtest: RS485 loopback
2022-06-25 Move TODO to the root directory
2022-06-25 Implemented a DFU bootloader
2022-06-25 mjtest: Add a script to run kermit
2022-06-25 Firmware: Init
2022-06-25 .gitignore
2022-06-25 Firmware: The first attempt at interface spec
2022-06-25 Firmware: Control requests
2022-06-25 Firmware: Bits of USB communication
2022-06-25 Firmware: Split to multiple source files
2022-06-26 Firmware: MODBUS mostly done
2022-06-26 Firmware: The rest of MODBUS
2022-06-26 Firmware: MODBUS debug messages
2022-06-26 Firmware: USB bug fixes
2022-06-26 A simple test program
2022-06-26 Firmware: Fixed flow control problems
2022-07-06 Firmware: MODBUS transmit debugged
2022-07-07 Interface: Enum for parity modes
2022-07-07 TODO: Another HW bug
2022-07-07 Firmware: Default parity should be EVEN
2022-07-07 Firmware: Fix bugs in MODBUS direction switching
2022-07-07 Test: More play
2022-07-07 Firmware: Better debug message
2022-07-07 Added an example MODBUS client device
2022-07-07 test-usbclient: urstest lives here
2022-07-08 Daemon: The first bits...
2022-07-09 test-device: Fix Makefile
2022-07-09 Firmware: Use protocol constants from modbus-proto.h
2022-07-09 Daemon: Communication with clients
2022-07-09 Daemon: Ports and queues
2022-07-09 Daemon: Split to multiple files, add USB stuff
2022-07-09 Daemon: Basic communication works
2022-07-09 Daemon: TODO
2022-07-09 test-pyclient: A trivial TCP MODBUS client
2022-07-09 Daemon: First bits of configuration
2022-07-12 Daemon: Preparing for support of multiple devices
    In most parts of the code, we use the "struct box" abstraction now.
    However, usb.c has to be rewritten to use USB hotplug before it can
    handle multiple boxes.
2022-07-12 Daemon: Control messages
2022-07-12 Daemon: Control messages debugged
2022-07-12 Daemon: Support for multiple switches and USB hot-plug
2022-07-12 Daemon: Cosmetics
2022-07-12 Daemon: Better logging
2022-07-12 Firmware: Keeping event counters
2022-07-12 Daemon: RX bulk transfers have no timeout
2022-07-12 Firmware: Fix bug in sending of port statistics
2022-07-12 Daemon: We distinguish user-facing port_number from hardware phys_number
2022-07-12 Daemon: Port statistics
2022-07-12 Daemon: Fix bug in tracking of busy messages at client's side
2022-07-12 Daemon: Fix orphaning of messages
2022-07-12 TODO
2022-07-13 Daemon: Initial log message
2022-07-13 Daemon: Do not crash when trying to control a disconnected device
2022-07-13 Utility: First experiments
2022-07-14 Utility: Configuration of ports
2022-07-15 TODO and FIXME
2022-07-15 Utility: Status of ports
2022-07-15 Utility: Catch MODBUS connection exceptions
2022-07-15 Daemon: Identification commands
2022-07-15 Utility: Version
2022-07-15 Firmware: Fixed format of internal error replies
2022-07-15 Daemon: Fix ID conformity level
2022-07-15 Utility: Bus scanning
2022-07-15 Fix numbering of ports
2022-07-15 TODO: Indentation
2022-07-15 Daemon: Ask for TCP_NODELAY
2022-07-15 Daemon: Persistent port configuration
2022-07-15 Daemon: Corking of clients
2022-07-15 Daemon: Configurable logging of connections
2022-07-15 Daemon: Proper configurable logging mechanism
2022-07-15 Daemon: Path to configuration file
2022-07-15 Daemon: Better log message
2022-07-15 Daemon: Still improving log messages
2022-07-17 Firmware: get_current_time()
    Quite tricky, but looks solid.
2022-07-17 Firmware: Port state structure
2022-07-17 Firmware: Proper inter-frame gaps
2022-07-18 Firmware: Activity LEDs
2022-07-18 Firmware: Configurable debug messages
2022-07-18 Firmware: Increase MAX_IN_FLIGHT
2022-07-18 Firmware: Shorter LED blinks
2022-07-18 test-pyclient: test2
2022-07-18 Daemon: Documented control interface
2022-07-18 Firmware: Resetting of port statistics
2022-07-18 Daemon: Upon USB error, cancel all transfers
    Otherwise, the RX transfer can hang indefinitely, preventing the
    broken state from being resolved.
2022-07-18 Daemon: Resetting of port statistics
2022-07-18 Utility: Resetting of port statistics
2022-11-02 3d model of a box in OpenSCAD.
2022-11-05 Fix port cutout offsets.
2022-11-13 Updated shape of power connector.
2023-04-08 TODO: Visible power LEDs
2023-04-08 Firmware: Flash LEDs during initialization
    Power/debugging LEDs are not visible through the case,
    so let us do something visible during switch initialization.
2023-05-13 Daemon: Implement port descriptions
2023-05-13 Utility: Implement port description config
2023-05-13 Utility: Show port description in status
2023-08-23 Utility: Compatibility with newer pymodbus (Debian Bookworm)
2023-08-23 Utility: Bug fix for previous commit

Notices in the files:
sw/firmware/main.c:
(c) 2022 Martin Mareš <mj@ucw.cz>
